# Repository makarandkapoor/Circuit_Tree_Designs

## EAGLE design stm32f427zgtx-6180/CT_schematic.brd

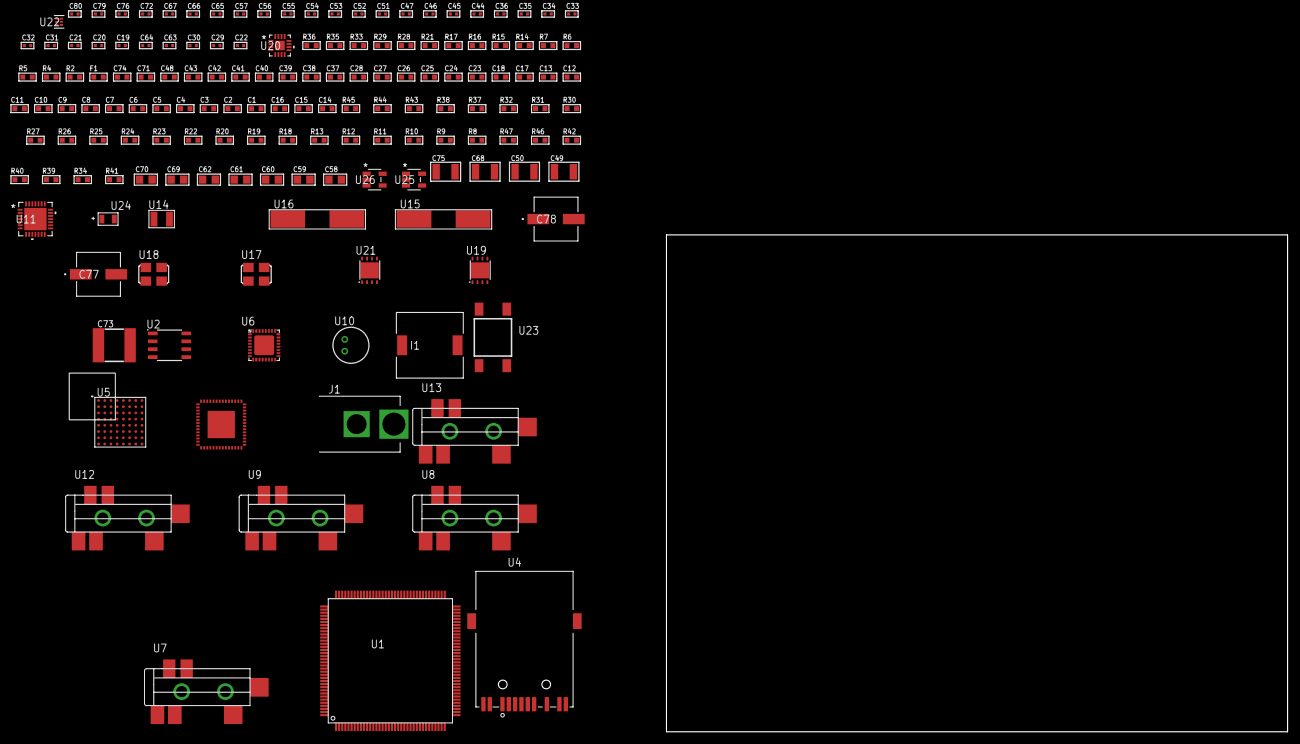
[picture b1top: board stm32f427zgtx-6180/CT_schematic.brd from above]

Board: 2 copper layers, 100.0 x 80.0 mm, 154 parts (0 on the bottom side), 149 nets, no tracks yet.

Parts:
C1, C18, C37, C38, C39, C40, C41, C42, C43, C48, C71: 1e-06; C0603
C2, C3, C4, C5, C6, C7, C8, C9, C10, C11, C12, C13, C23, C24, C25, C26, C27, C28: 1e-07; C0603
C14: 4.7e-06; C0603
C15, C16: 2.2e-06; C0603
C17: 1e-08; C0603
C19, C20: 1e-11; C0402
C21, C32, C34, C36, C65, C66, C67, C79, C80: 1e-08; C0402
C22: 2.2e-08; C0402
C29, C30, C63, C64: 2.2e-11; C0402
C31, C33, C35, C44, C45, C46, C47, C53, C54, C55, C56, C57, C72, C76: 1e-07; C0402
C49, C50: 2.2e-05; C1210
C51, C52: 1e-09; C0402
C58, C59, C60, C61, C62, C69, C70: 1e-05; C0805
C68, C75: 1e-05; C1210
C73: 6.8e-05; 2220
C74: 8e-07; R0603
C77, C78: 0.0001; EXV-9H
F1: 240.0; L0603
I1: 5.2e-06; DR1040
J1: PJ-037B; PJ-037B_PACKAGE
R2, R36: 1000.0; R0603
R4, R5: 4700.0; R0603
R6, R7: 2200.0; R0603
R8, R9, R10, R11, R12, R13, R18, R19, R20, R22, R23, R24, R25, R26, R27, R43, R44: 10000.0; R0603
R14, R15: 0.1; R0603
R16, R17, R35: 200.0; R0603
R21: 2000.0; R0603
R28, R29: 1270.0; R0603
R30, R31, R32: 47000.0; R0603
R33: 680.0; R0603
R34, R40, R42: 100000.0; R0603
R37: 20000.0; R0603
R38: 62000.0; R0603
R39: 300000.0; R0603
R41: 153694.38; R0603
R45: 18000.0; R0603
R46: 470000.0; R0603
R47: 120000.0; R0603
U1: STM32F427ZGT6; LQFP144
U2: AT25512N-SH-T; SOIC-8
U3: 88E3015A2NNP1C000
U4: 7498011122R
U5: PC28F512P33BFD
U6: SGTL5000XNAA3; QFN-32
U7, U8, U9, U12, U13: SJ-43515TS-SMT-TR
U10: WM-64PCT; WM-64PC
U11: WM8731CLSEFL; QFN-28
U14: ABS07-32.768KHZ-7-T
U15: ABLS-25.000MHZ-B2F-T
U16: ABLS-12.288MHZ-B4-T
U17: ASFL-24.57MHZ-NCS; ASFL1
U18: ASFL1-25MHZ-NCS; ASFL1
U19: LP3878SDX-ADJ/NOPB; WSON-8
U20: LTC3601EUD#PBF; QFN-16_EP
U21: LP2951ACSDX/NOPB; WSON-8
U22: TPS3895ADRYR; SON-6
U23: 4-1437565-2; SW_4-1437565-2
U24: Q65110A2395; LGM67K-G1J2-24-Z
U25, U26: nc7sz125m5x; NC7SZ125M5X

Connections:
CLK_CRYSTAL_U1_8: C19.1, U1.8, U14.1
CLK_CRYSTAL_U1_9: C20.1, U1.9, U14.2
CLK_CRYSTAL_U3_32: C29.1, U3.32, U15.1
CLK_CRYSTAL_U3_33: C30.1, U3.33, U15.2
CLK_CRYSTAL_U11_1: C63.1, U11.1, U16.1
CLK_CRYSTAL_U11_2: C64.1, U11.2, U16.2
CLK_U1_23: U1.23, U18.3
CLK_U6_21: U6.21, U17.3
GND: C1.2, C2.2, C3.2, C4.2, C5.2, C6.2, C7.2, C8.2, C9.2, C10.2, C11.2, C12.2, C13.2, C14.2, C15.2, C16.2, C17.2, C18.2, C19.2, C20.2, C21.2, C22.2, C23.2, C24.2, C25.2, C26.2, C27.2, C28.2, C29.2, C30.2, C31.2, C32.2, C33.2, C34.2, C35.2, C36.2, C44.2, C45.2, C46.2, C47.2, C48.2, C52.2, C53.2, C54.2, C55.2, C56.2, C57.2, C58.2, C59.2, C60.2, C61.2, C62.2, C63.2, C64.2, C65.2, C66.2, C67.2, C68.2, C69.2, C70.2, C71.2, C73.1, C73.2, C74.2, C75.2, C76.2, C77.2, C78.2, C79.2, C80.2, J1.2, R2.2, R14.2, R15.2, R21.2, R29.2, R30.2, R31.2, R32.2, R36.2, R37.2, R39.2, R42.2, R45.2, R47.2, U1.16, U1.31, U1.38, U1.51, U1.61, U1.83, U1.94, U1.107, U1.120, U1.130, U2.4, U3.1, U3.2, U3.57, U4.10, U4.12, U5.B2, U5.H2, U5.H4, U5.H6, U6.1, U6.3, U6.7, U6.EXP, U8.1, U9.1, U10.2, U11.4, U11.15, U11.19, U11.25, U11.26, U11.29, U12.1, U13.1, U17.2, U18.2, U19.3, U19.PAD, U20.1, U20.9, U20.17, U21.3, U21.4, U21.PAD, U22.2, U24.C, U25.1, U25.3, U26.1, U26.3
NET_U1_25: R5.1, U1.25, U26.4
NET_U1_27: R6.1, U1.27, U3.38
NET_U1_33: C17.1, C18.1, F1.1, U1.32, U1.33
NET_U1_36: R7.1, U1.36, U3.35
NET_U1_48: R10.1, U1.48
NET_U1_71: C15.1, U1.71
NET_U1_106: C16.1, U1.106
NET_U1_138: R9.1, U1.138
NET_U1_142: U23.3, U23.4
NET_U1_143: R8.1, U1.143
NET_U2_3: R11.1, U2.3
NET_U2_7: R13.1, U2.7
NET_U3_9: R19.1, U3.9
NET_U3_10: R22.1, U3.10
NET_U3_16: R18.1, U3.16
NET_U3_28: R21.1, U3.28
NET_U3_39: R20.1, U3.39
NET_U3_44: U3.44, U3.48, U3.49, U3.56
NET_U4_1: U3.26, U4.1
NET_U4_3: U3.25, U4.3
NET_U4_4: U3.23, U4.4
NET_U4_5: C22.1, U4.2, U4.5
NET_U4_6: U3.22, U4.6
NET_U4_8: R15.1, R17.2, U4.8
NET_U4_9: R16.1, U4.9
NET_U4_11: R17.1, U4.11
NET_U4_13: R14.1, U4.13, U4.14
NET_U5_A4: C35.1, C36.1, U5.A4
NET_U5_C6: R26.1, U5.C6
NET_U5_D4: R4.1, U5.D4, U25.4
NET_U6_10: C47.1, U6.10
NET_U6_29: R28.1, U6.29
NET_U6_31: R29.1, U6.31
NET_U7_1: U6.4, U7.1
NET_U7_2: U6.2, U7.2
NET_U7_5: U6.6, U7.5
NET_U8_2: C38.1, U8.2
NET_U8_5: C37.1, U8.5
NET_U9_2: C40.1, C41.1, U9.2
NET_U9_5: C39.1, U9.5
NET_U9_13: C40.2, C41.2
NET_U10_1: C42.1, C43.1, C48.1, U6.16, U10.1
NET_U10_15: C42.2, C43.2
NET_U11_20: C57.1, C62.1, U11.20
NET_U12_2: C50.1, R31.1, U12.2
NET_U12_5: C49.1, R30.1, U12.5
NET_U13_5: C51.1, C52.1, R32.1, R33.1, U13.5
NET_U19_1: C67.1, U19.1
NET_U19_6: R35.2, R36.1, U19.6
NET_U19_8: R34.1, U19.8
NET_U20_3: C72.2, I1.1, U20.3, U20.4
NET_U20_6: C72.1, U20.6
NET_U20_7: C71.1, U20.7, U20.12
NET_U20_10: R39.1, U20.10
NET_U20_11: R37.1, R38.1, U20.11
NET_U20_ATNET_3: I1.2, R38.2
NET_U21_5: R40.1, U21.5
NET_U21_7: R41.2, R42.1, U21.7
NET_U22_1: R44.1, R45.1, U22.1
NET_U22_3: R46.2, R47.1, U22.3
NET_U22_4: R43.1, U22.4, U25.2, U26.2
NET_U23_1: R2.1, U23.1, U23.2
PROC_ETH_COL: U1.37, U3.3, U3.19
PROC_ETH_CRS: U1.34, U3.18
PROC_ETH_RXD0: U1.44, U3.42
PROC_ETH_RXD1: U1.45, U3.43
PROC_ETH_RXD2: U1.46, U3.46
PROC_ETH_RXD3: U1.47, U3.47
PROC_ETH_RX_CLK: U1.35, U3.45
PROC_ETH_RX_DV: U1.43, U3.41
PROC_ETH_RX_ER: U1.69, U3.17
PROC_ETH_TXD0: U1.73, U3.50
PROC_ETH_TXD1: U1.129, U3.51
PROC_ETH_TXD2: U1.28, U3.53
PROC_ETH_TXD3: U1.139, U3.54
PROC_ETH_TX_CLK: U1.29, U3.52
PROC_ETH_TX_EN: U1.70, U3.55
PROC_FMC_A0: U1.10, U5.A1
PROC_FMC_A1: U1.11, U5.B1
PROC_FMC_A2: U1.12, U5.C1
PROC_FMC_A3: U1.13, U5.D1
PROC_FMC_A4: U1.14, U5.D2
PROC_FMC_A5: U1.15, U5.A2
PROC_FMC_A6: U1.50, U5.C2
PROC_FMC_A7: U1.53, U5.A3
PROC_FMC_A8: U1.54, U5.B3
PROC_FMC_A9: U1.55, U5.C3
PROC_FMC_A10: U1.56, U5.D3
PROC_FMC_A11: U1.57, U5.C4
PROC_FMC_A12: U1.87, U5.A5
PROC_FMC_A13: U1.88, U5.B5
PROC_FMC_A14: U1.89, U5.C5
PROC_FMC_A15: U1.90, U5.D7
PROC_FMC_A16: U1.80, U5.D8
PROC_FMC_A17: U1.81, U5.A7
PROC_FMC_A18: U1.82, U5.B7
PROC_FMC_A19: U1.2, U5.C7
PROC_FMC_A20: U1.3, U5.C8
PROC_FMC_A21: U1.4, U5.A8
PROC_FMC_A22: U1.5, U5.G1
PROC_FMC_A23: U1.1, U5.H8
PROC_FMC_A24: U1.128, U5.B6
PROC_FMC_CLK: U1.117, U5.E6
PROC_FMC_D0: U1.85, U5.F2
PROC_FMC_D1: U1.86, U5.E2
PROC_FMC_D2: U1.114, U5.G3
PROC_FMC_D3: U1.115, U5.E4
PROC_FMC_D4: U1.58, U5.E5
PROC_FMC_D5: U1.59, U5.G5
PROC_FMC_D6: U1.60, U5.G6
PROC_FMC_D7: U1.63, U5.H7
PROC_FMC_D8: U1.64, U5.E1
PROC_FMC_D9: U1.65, U5.E3
PROC_FMC_D10: U1.66, U5.F3
PROC_FMC_D11: U1.67, U5.F4
PROC_FMC_D12: U1.68, U5.F5
PROC_FMC_D13: U1.77, U5.H5
PROC_FMC_D14: U1.78, U5.G7
PROC_FMC_D15: U1.79, U5.E7
PROC_FMC_NE2: R24.1, U1.124, U5.B4
PROC_FMC_NL: R23.1, U1.137, U5.F6
PROC_FMC_NOE: R25.1, U1.118, U5.F8
PROC_FMC_NWAIT: U1.122, U5.F7
PROC_FMC_NWE: R27.1, U1.119, U5.G8
PROC_I2S2_CK: U1.74, U11.7
PROC_I2S2_EXT_SD: U1.75, U11.10
PROC_I2S2_SD: U1.76, U11.8
PROC_I2S2_WS: U1.140, U11.9, U11.11
PROC_I2S3_CK: U1.111, U6.24
PROC_I2S3_EXT_SD: U1.112, U6.25
PROC_I2S3_SD: U1.113, U6.26
PROC_I2S3_WS: U1.110, U6.23
PROC_SPI1_MISO: U1.42, U2.2
PROC_SPI1_MOSI: U1.135, U2.5
PROC_SPI1_NSS: R12.1, U1.40, U2.1
PROC_SPI1_SCK: U1.41, U2.6
VCC_S1_12V9: C68.1, C70.1, C74.1, C77.1, C78.1, J1.1, R34.2, U19.4, U20.15, U20.16, U21.8
VCC_TIER1_1V2: C23.1, C24.1, C44.1, C69.1, R35.1, U3.4, U3.11, U3.34, U6.30, U19.5
VCC_TIER1_2V5: C1.1, C2.1, C3.1, C4.1, C5.1, C6.1, C7.1, C8.1, C9.1, C10.1, C11.1, C12.1, C13.1, C14.1, C21.1, C25.1, C26.1, C27.1, C28.1, C31.1, C32.1, C33.1, C34.1, C45.1, C46.1, C53.1, C54.1, C55.1, C56.1, C58.1, C59.1, C60.1, C61.1, C73.2, C76.1, C79.1, C80.1, F1.2, I1.2, R4.2, R5.2, R6.2, R7.2, R8.2, R9.2, R10.2, R11.2, R12.2, R13.2, R18.2, R19.2, R20.2, R22.2, R23.2, R24.2, R25.2, R26.2, R27.2, R28.2, R38.2, R43.2, R44.2, R46.1, U1.6, U1.17, U1.30, U1.39, U1.52, U1.62, U1.72, U1.84, U1.95, U1.108, U1.121, U1.131, U1.144, U2.8, U3.6, U3.12, U3.13, U3.20, U3.24, U3.29, U3.36, U4.2, U5.A6, U5.D5, U5.D6, U5.G4, U5.H3, U6.5, U6.20, U11.3, U11.5, U11.12, U11.18, U20.8, U22.6, U25.5, U26.5
VCC_TIER1_3V3: C65.1, C66.1, C75.1, R40.2, R41.1, U17.4, U18.4, U21.1

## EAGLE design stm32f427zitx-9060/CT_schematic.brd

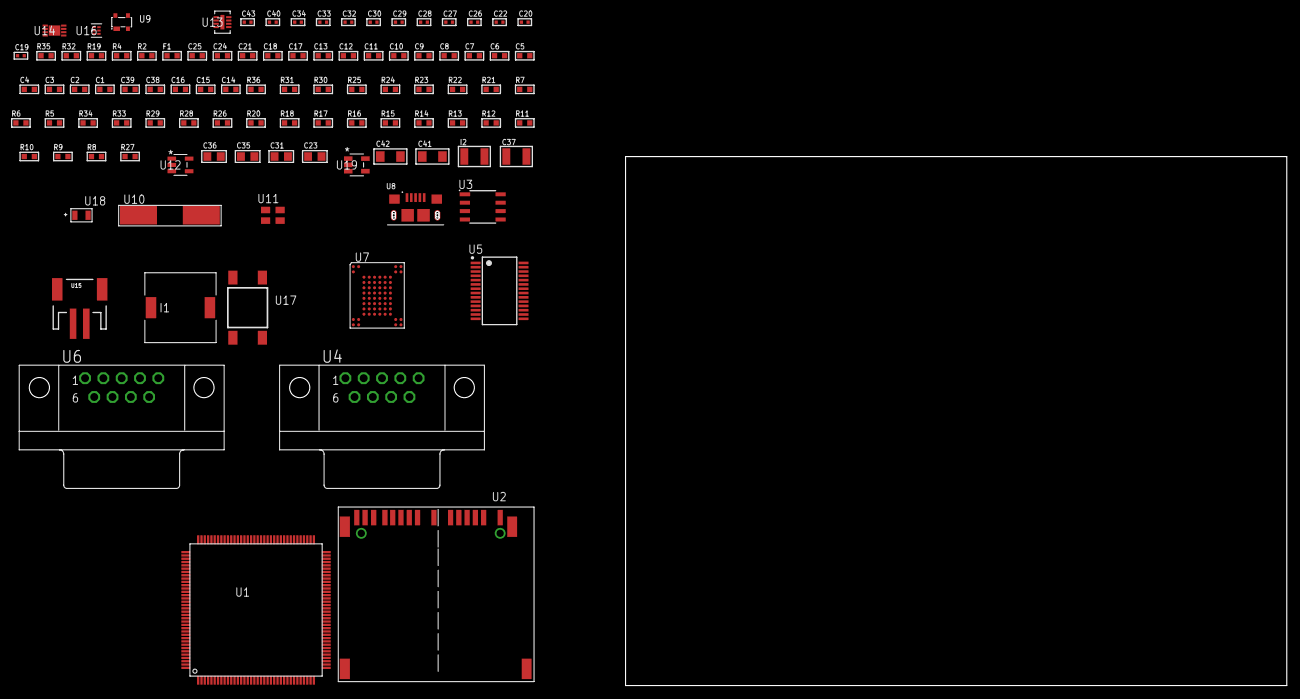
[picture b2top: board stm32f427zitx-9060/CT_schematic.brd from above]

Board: 2 copper layers, 99 parts (0 on the bottom side), 76 nets, no tracks yet.

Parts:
C1, C18, C21, C24, C25: 1e-06; C0603
C2, C3, C4, C5, C6, C7, C8, C9, C10, C11, C12, C13: 1e-07; C0603
C14: 4.7e-06; C0603
C15, C16, C38: 2.2e-06; C0603
C17: 1e-08; C0603
C19, C20: 1e-11; C0402
C22, C26, C27, C28, C29, C30, C32, C33, C40: 1e-07; C0402
C23, C31, C35, C36: 1e-05; C0805
C34, C43: 1e-08; C0402
C37: 1e-05; C1210
C39: 2.2e-07; C0603
C41, C42: 1e-05; C1206
F1: 240.0; L0603
I1: 2.5e-06; DR1040
I2: 1e-05; L1210
R2: 1000.0; R0603
R4: 4700.0; R0603
R5, R6, R7, R21, R22, R23, R24, R25, R30, R31, R36: 10000.0; R0603
R8, R9, R10, R11, R12, R13, R14, R15, R16, R17, R18, R20, R28: 100000.0; R0603
R19: 120.0; R0603
R26: 220000.0; R0603
R27: 1000000.0; R0603
R29: 560000.0; R0603
R32: 9100.0; R0603
R33: 680000.0; R0603
R34: 120000.0; R0603
R35: 2000.0; R0603
U1: STM32F427ZIT7; LQFP144
U2: 10100565
U3: MCP2562-E/SN; SOIC-8
U4, U6: 182-009-113R531; 182-009-MALE
U5: ST3241EBPR; SSOP-28
U7: TH58NVG3S0HBAI4
U8: 10118193-0001LF; FCI_10118193-0001LF
U9: prtr5v0u2ax; SOT143B
U10: ABLS-25.000MHZ-B2F-T
U11: ASEK-32.768KHz-ECST; ASEK
U12: ltc3406es5; TSOT-23-5
U13: LT3494AEDDB#TRMPBF; DFN-8_DDB
U14: MCP73831T-2ACI/MC; DFN8_2X3MC
U15: S2B-PH-SM4-TB(LF)(SN); JST-2-SMD
U16: TPS3895ADRYR; SON-6
U17: 4-1437565-2; SW_4-1437565-2
U18: Q65110A2395; LGM67K-G1J2-24-Z
U19: nc7sz125m5x; NC7SZ125M5X

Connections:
CLK_CRYSTAL_U1_23: C19.1, U1.23, U10.1
CLK_CRYSTAL_U1_24: C20.1, U1.24, U10.2
CLK_U1_8: U1.8, U11.3
GND: C1.2, C2.2, C3.2, C4.2, C5.2, C6.2, C7.2, C8.2, C9.2, C10.2, C11.2, C12.2, C13.2, C14.2, C15.2, C16.2, C17.2, C18.2, C19.2, C20.2, C21.2, C22.2, C23.2, C24.2, C25.2, C26.2, C29.2, C30.2, C31.2, C32.2, C33.2, C34.2, C35.2, C36.1, C36.2, C37.2, C38.2, C39.2, C40.2, C41.2, C42.2, C43.2, R2.2, R7.2, R26.2, R32.2, R34.2, R35.2, U1.16, U1.31, U1.38, U1.51, U1.61, U1.83, U1.94, U1.103, U1.107, U1.120, U1.130, U2.6, U2.10, U2.12, U2.16, U2.17, U2.20, U2.21, U3.2, U3.8, U4.5, U5.23, U5.25, U6.5, U7.C5, U7.K3, U7.K8, U8.5, U8.6, U8.7, U8.8, U8.9, U9.1, U11.2, U12.2, U13.2, U13.9, U14.6, U14.9, U15.2, U16.2, U18.C, U19.1, U19.3
INPUT_USBPOWER_5V: C21.1, C41.1, R36.2, U1.101, U8.1, U9.4, U14.1, U14.2
NET_U1_25: R4.1, U1.25, U19.4
NET_U1_33: C17.1, C18.1, F1.1, U1.32, U1.33
NET_U1_48: R7.1, U1.48
NET_U1_71: C15.1, U1.71
NET_U1_106: C16.1, U1.106
NET_U1_138: R6.1, U1.138
NET_U1_142: U17.3, U17.4
NET_U1_143: R5.1, U1.143
NET_U2_1: R10.1, U2.1
NET_U2_2: R9.1, U2.2
NET_U2_18: U2.18, U2.19
NET_U3_6: R19.2, U3.6
NET_U4_2: R19.2, U3.6, U4.2
NET_U4_3: R19.1, U3.7, U4.3
NET_U5_1: C28.1, U5.1
NET_U5_2: C28.2, U5.2
NET_U5_3: C30.1, U5.3
NET_U5_22: R20.1, U5.22
NET_U5_24: C27.2, U5.24
NET_U5_27: C29.1, U5.27
NET_U5_28: C27.1, U5.28
NET_U6_2: U5.4, U6.2
NET_U6_3: U5.9, U6.3
NET_U6_7: U5.5, U6.7
NET_U6_8: U5.10, U6.8
NET_U7_C3: R24.1, U7.C3
NET_U12_3: I1.1, U12.3
NET_U12_5: R26.1, R27.1, U12.5
NET_U12_ATNET_3: I1.2, R27.2
NET_U13_1: I2.1, U13.1
NET_U13_5: R28.1, U13.5
NET_U13_6: R29.1, U13.6
NET_U13_8: C39.1, U13.8
NET_U14_5: R36.1, U14.5
NET_U14_8: R35.1, U14.8
NET_U16_1: R31.1, R32.1, U16.1
NET_U16_3: R33.2, R34.1, U16.3
NET_U16_4: R30.1, U16.4, U19.2
NET_U17_1: R2.1, U17.1, U17.2
PROC_CAN2_RX: U1.73, U3.4
PROC_CAN2_TX: U1.74, U3.1
PROC_FMC_A16: U1.80, U7.D5
PROC_FMC_A17: U1.81, U7.C4
PROC_FMC_D0: U1.85, U7.H4
PROC_FMC_D1: U1.86, U7.J4
PROC_FMC_D2: U1.114, U7.K4
PROC_FMC_D3: U1.115, U7.K5
PROC_FMC_D4: U1.58, U7.K6
PROC_FMC_D5: U1.59, U7.J7
PROC_FMC_D6: U1.60, U7.K7
PROC_FMC_D7: U1.63, U7.J8
PROC_FMC_INT2: R25.1, U1.91, U7.C8
PROC_FMC_NCE2: R21.1, U1.123, U7.C6
PROC_FMC_NOE: R22.1, U1.118, U7.D4
PROC_FMC_NWE: R23.1, U1.119, U7.C7
PROC_SDIO_CK: R8.1, U1.113, U2.8
PROC_SDIO_D0: R11.1, U1.98, U2.4
PROC_SDIO_D1: R12.1, U1.99, U2.3
PROC_SDIO_D2: R13.1, U1.111, U2.15
PROC_SDIO_D3: R14.1, U1.112, U2.14
PROC_SDIO_D4: R15.1, U1.139, U2.13
PROC_SDIO_D5: R16.1, U1.140, U2.11
PROC_SDIO_D6: R17.1, U1.96, U2.7
PROC_SDIO_D7: R18.1, U1.97, U2.5
PROC_UART4_RX: U1.35, U5.19
PROC_UART4_TX: U1.34, U5.14
PROC_USB_OTG_FS_DM: U1.103, U8.2, U9.3
PROC_USB_OTG_FS_DP: U1.104, U8.3, U9.2
VCC_S1_3V7: C35.1, C37.1, C42.1, I2.2, R28.2, U12.4, U13.3, U13.4, U14.3, U14.4, U15.1
VCC_TIER1_3V3: C1.1, C2.1, C3.1, C4.1, C5.1, C6.1, C7.1, C8.1, C9.1, C10.1, C11.1, C12.1, C13.1, C14.1, C22.1, C23.1, C25.1, C26.1, C31.1, C32.1, C33.1, C34.1, C36.2, C40.1, C43.1, F1.2, I1.2, R4.2, R5.2, R6.2, R8.2, R9.2, R10.2, R11.2, R12.2, R13.2, R14.2, R15.2, R16.2, R17.2, R18.2, R20.2, R21.2, R22.2, R23.2, R24.2, R25.2, R27.2, R30.2, R31.2, R33.1, U1.6, U1.17, U1.30, U1.39, U1.52, U1.62, U1.72, U1.84, U1.95, U1.108, U1.121, U1.131, U1.144, U2.9, U3.5, U5.26, U7.H8, U7.J6, U11.4, U16.6, U19.5
VCC_TIER1_5V0: C24.1, C38.1, R29.2, U3.3, U13.7

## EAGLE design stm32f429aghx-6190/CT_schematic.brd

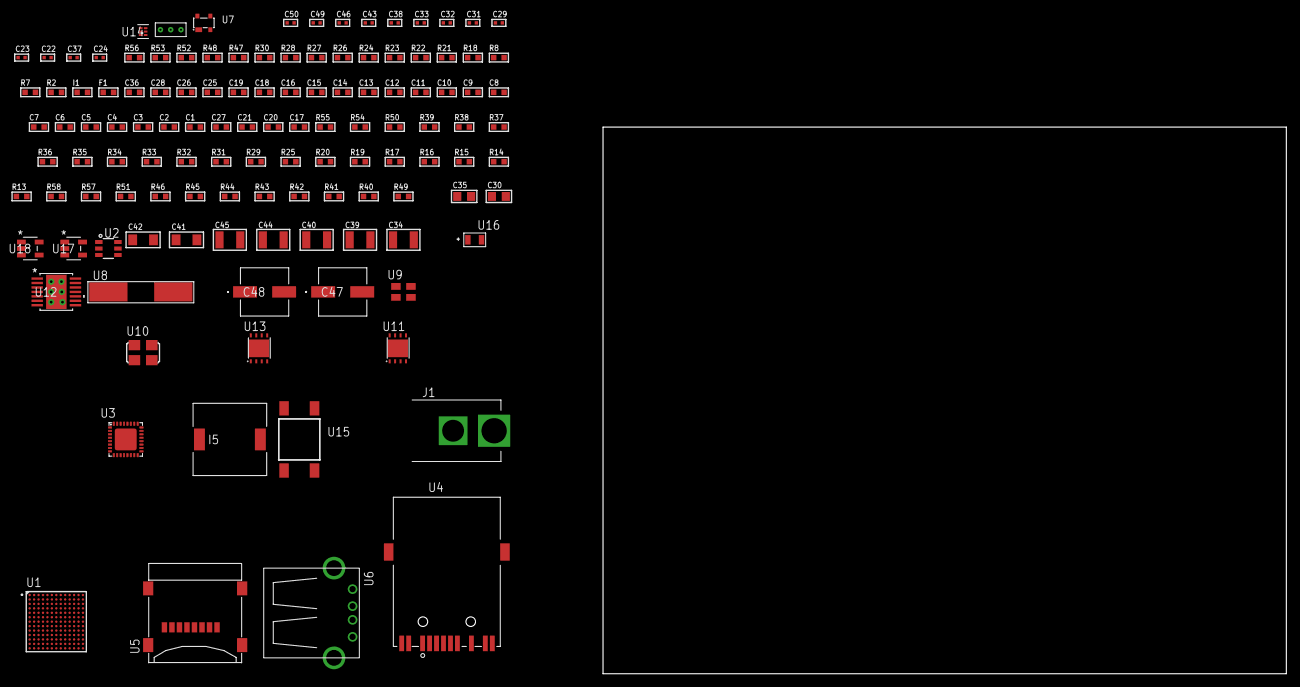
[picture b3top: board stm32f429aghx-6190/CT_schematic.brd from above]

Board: 2 copper layers, 100.0 x 80.0 mm, 122 parts (0 on the bottom side), 70 nets, no tracks yet.

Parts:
C1, C19, C25, C26, C28, C36: 1e-06; C0603
C2, C3, C4, C5, C6, C7, C8, C9, C10, C11, C12, C13, C14, C15, C16: 1e-07; C0603
C17: 4.7e-06; C0603
C18: 1e-08; C0603
C20, C21: 2.2e-06; C0603
C22, C23: 1e-11; C0402
C24: 2.2e-08; C0402
C27: 4.7e-10; C0603
C29, C38, C46: 1e-07; C0402
C30, C35: 1e-05; C0805
C31, C32, C33, C43, C49, C50: 1e-08; C0402
C34, C44, C45: 1e-05; C1210
C37: 3.3e-09; C0402
C39, C40: 2.2e-05; C1210
C41, C42: 1e-05; C1206
C47, C48: 0.0001; EXV-9H
F1: 240.0; L0603
I1: 97.0; R0603
I5: 3.8e-06; DR1040
J1: PJ-037B; PJ-037B_PACKAGE
R2, R48, R53: 1000.0; R0603
R7, R8: 4700.0; R0603
R13: 47000.0; R0603
R14, R15, R16, R17, R19, R20, R29, R31, R32, R33, R34, R35, R36, R37, R38, R39, R54, R55: 10000.0; R0603
R18: 1270.0; R0603
R21, R22: 0.1; R0603
R23, R24, R47: 200.0; R0603
R25: 12100.0; R0603
R26, R27, R28, R30: 49.9; R0603
R40, R41, R42, R43, R44, R45, R46, R51: 100000.0; R0603
R49: 71007.101651032; R0603
R50: 22000.0; R0603
R52: 3900.0; R0603
R56: 9100.0; R0603
R57: 680000.0; R0603
R58: 120000.0; R0603
U1: STM32F429AGH6; UFBGA169
U2: MAX4995AAUT+T; SOT-23-6
U3: LAN8710AI-EZK; QFN-32
U4: 7498011122R
U5: 0472192001; MOLEX_47219-2001
U6: 61400416021; USB-A-H
U7: prtr5v0u2ax; SOT143B
U8: ABLS-25.000MHZ-B2F-T
U9: ASEK-32.768KHz-ECST; ASEK
U10: ASFL1-50MHZ-NCS; ASFL1
U11, U13: LP3878SDX-ADJ/NOPB; WSON-8
U12: TPS54425PWP; HTSSOP14
U14: TPS3895ADRYR; SON-6
U15: 4-1437565-2; SW_4-1437565-2
U16: Q65110A2395; LGM67K-G1J2-24-Z
U17, U18: nc7sz125m5x; NC7SZ125M5X
U19: Dummy; DUMMY_PACKAGE_243

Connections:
CLK_CRYSTAL_U1_G1: C22.1, U1.G1, U8.1
CLK_CRYSTAL_U1_G2: C23.1, U1.G2, U8.2
CLK_U1_E1: U1.E1, U9.3
CLK_U1_K1: U1.K1, U10.3
GND: C1.2, C2.2, C3.2, C4.2, C5.2, C6.2, C7.2, C8.2, C9.2, C10.2, C11.2, C12.2, C13.2, C14.2, C15.2, C16.2, C17.2, C18.2, C19.2, C20.2, C21.2, C22.2, C23.2, C24.2, C25.2, C26.2, C27.2, C28.2, C29.2, C30.2, C31.2, C32.2, C33.2, C34.2, C35.2, C36.2, C37.2, C39.2, C40.2, C41.2, C42.2, C43.2, C44.2, C45.2, C46.2, C47.2, C48.2, C49.2, C50.2, J1.2, R2.2, R13.2, R17.2, R18.2, R20.2, R21.2, R22.2, R23.2, R25.2, R31.2, R38.2, R39.2, R48.2, R50.2, R53.2, R56.2, R58.2, U1.D7, U1.D11, U1.E7, U1.F5, U1.F6, U1.G7, U1.G9, U1.J1, U1.J2, U1.J6, U1.J7, U1.J10, U2.2, U3.24, U3.25, U3.EXP, U5.6, U5.G1, U5.G2, U5.G3, U5.G4, U6.4, U6.5, U6.6, U7.1, U9.2, U10.2, U11.3, U11.PAD, U12.5, U12.8, U12.9, U12.15, U13.3, U13.PAD, U14.2, U16.C, U17.1, U17.3, U18.1, U18.3, U19.1
NET_U1_A5: R15.1, U1.A5
NET_U1_C3: R14.1, U1.C3
NET_U1_D12: C21.1, U1.D12
NET_U1_E9: R18.1, U1.E9
NET_U1_H2: R8.1, U1.H2, U18.4
NET_U1_J4: C18.1, C19.1, F1.1, U1.J3, U1.J4
NET_U1_L5: R16.1, U1.L5
NET_U1_M1: R17.1, U1.M1
NET_U1_N9: C20.1, U1.N9
NET_U1_N11: U15.3, U15.4
NET_U2_3: R13.1, U2.3
NET_U3_1: C25.1, I1.1, R26.2, R27.2, R28.2, R30.2, R33.2, U3.1, U3.27, U4.2, U4.9
NET_U3_3: R33.1, U3.3
NET_U3_7: R38.1, U3.7
NET_U3_8: R39.1, U3.8
NET_U3_9: R31.1, R32.1, U3.9
NET_U3_13: R37.1, U3.13
NET_U3_18: R29.1, U3.18
NET_U3_19: R7.1, U3.19, U17.4
NET_U3_32: R25.1, U3.32
NET_U4_1: R26.1, U3.29, U4.1
NET_U4_3: R24.2, R27.1, U3.28, U4.3
NET_U4_4: R28.1, U3.31, U4.4
NET_U4_5: C24.1, U4.2, U4.5
NET_U4_6: R30.1, U3.30, U4.6
NET_U4_8: R22.1, U4.8
NET_U4_10: R24.1, U4.10
NET_U4_11: U3.2, U4.11
NET_U4_12: R23.1, U4.12
NET_U4_13: R21.1, U4.13, U4.14
NET_U11_1: C33.1, U11.1
NET_U11_6: R47.2, R48.1, U11.6
NET_U11_8: R46.1, U11.8
NET_U12_2: R49.2, R50.1, U12.2
NET_U12_3: C36.1, U12.3
NET_U12_4: C37.1, U12.4
NET_U12_10: C38.1, I5.1, U12.10, U12.11
NET_U12_12: C38.2, U12.12
NET_U13_1: C43.1, U13.1
NET_U13_6: R52.2, R53.1, U13.6
NET_U13_8: R51.1, U13.8
NET_U14_1: R55.1, R56.1, U14.1
NET_U14_3: R57.2, R58.1, U14.3
NET_U14_4: R54.1, U14.4, U17.2, U18.2
NET_U15_1: R2.1, U15.1, U15.2
PROC_ETH_CRS_DV: R36.1, U3.15
PROC_ETH_RXD0: R34.1, U3.11
PROC_ETH_RXD1: R35.1, U3.10
PROC_GPIO_TO_U1_USB_FAULT: R19.1, U1.A3, U2.6
PROC_GPIO_TO_U1_VBUS_EN: R20.1, U1.A2, U2.4
PROC_SDIO_CK: R41.1, U1.A10, U5.5
PROC_SDIO_CMD: R40.1, U1.B9, U5.3
PROC_SDIO_D0: R42.1, U1.F11, U5.7
PROC_SDIO_D1: R43.1, U1.F12, U5.8
PROC_SDIO_D2: R44.1, U1.C10, U5.1
PROC_SDIO_D3: R45.1, U1.B10, U5.2
PROC_TIM1_CH1: U1.E13, U19.2
PROC_TIM1_CH2N: U1.L8, U19.3
PROC_USB_OTG_FS_DM: U1.E10, U6.2, U7.3
PROC_USB_OTG_FS_DP: U1.E11, U6.3, U7.2
PROC_USB_OTG_FS_VBUS: U1.E8, U2.1, U6.1, U7.4
VCC_S1_14V5: C34.1, C41.1, C42.1, C44.1, C47.1, C48.1, J1.1, R46.2, R51.2, U11.4, U12.7, U12.13, U12.14, U13.4
VCC_TIER1_1V2: C26.1, C27.1, C35.1, R47.1, U3.6, U11.5
VCC_TIER1_3V3: C1.1, C2.1, C3.1, C4.1, C5.1, C6.1, C7.1, C8.1, C9.1, C10.1, C11.1, C12.1, C13.1, C14.1, C15.1, C16.1, C17.1, C28.1, C29.1, C30.1, C31.1, C32.1, C39.1, C40.1, C46.1, C49.1, C50.1, F1.2, I1.2, I5.2, R7.2, R8.2, R14.2, R15.2, R16.2, R19.2, R29.2, R32.2, R34.2, R35.2, R36.2, R37.2, R40.2, R41.2, R42.2, R43.2, R44.2, R45.2, R49.1, R54.2, R55.2, R57.1, U1.D3, U1.D6, U1.D10, U1.E5, U1.E6, U1.F4, U1.F7, U1.F8, U1.G8, U1.G10, U1.H4, U1.H8, U1.J11, U1.K6, U1.L6, U3.12, U5.4, U9.4, U10.4, U12.1, U14.6, U17.5, U18.5
VCC_TIER1_5V0: C45.1, R52.1, U2.5, U13.5

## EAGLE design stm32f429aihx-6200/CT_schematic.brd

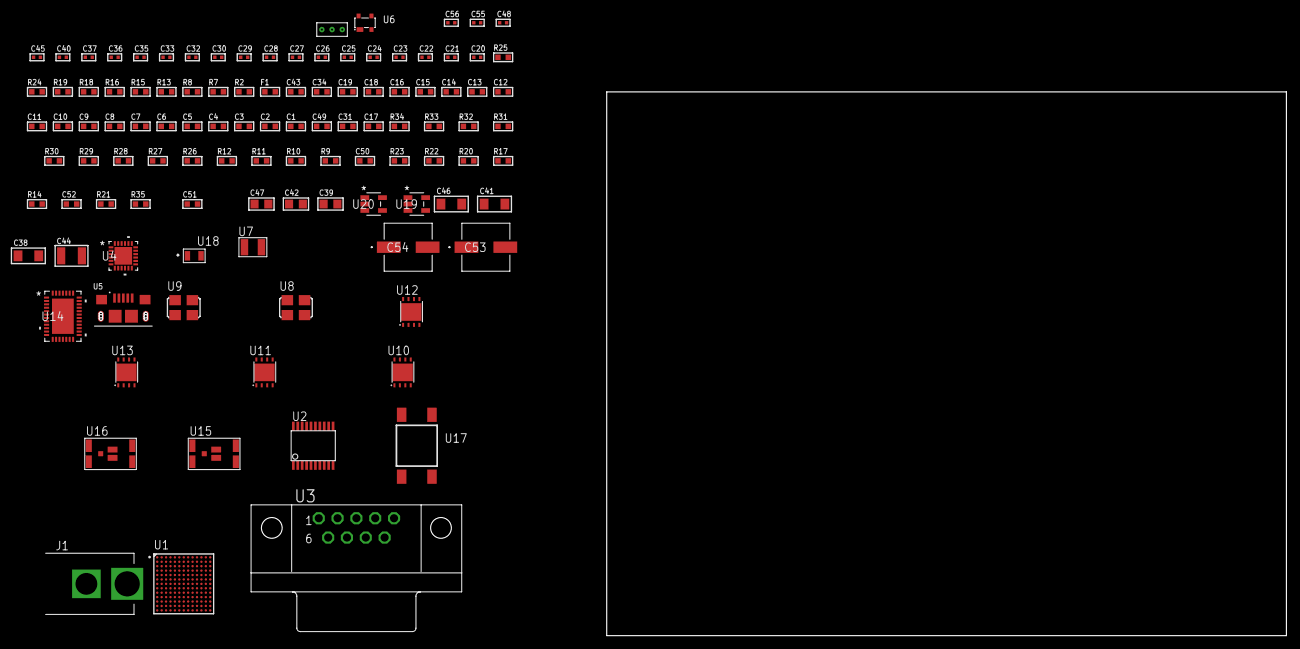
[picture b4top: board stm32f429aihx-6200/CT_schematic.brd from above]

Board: 2 copper layers, 109 parts (0 on the bottom side), 78 nets, no tracks yet.

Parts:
C1, C19, C34, C43: 1e-06; C0603
C2, C3, C4, C5, C6, C7, C8, C9, C10, C11, C12, C13, C14, C15, C16: 1e-07; C0603
C17: 4.7e-06; C0603
C18: 1e-08; C0603
C20, C21, C24, C25, C26, C27, C28, C29, C48: 1e-07; C0402
C22, C23: 1e-11; C0402
C30, C32, C33, C35, C36, C37, C40, C45, C55, C56: 1e-08; C0402
C31, C49: 2.2e-06; C0603
C38, C41, C46: 1e-05; C1206
C39, C42, C47: 1e-05; C0805
C44: 1e-05; C1210
C50: 2.45e-08; R0603
C51: 2.8258362168397e-09; R0603
C52: 7.105e-09; R0603
C53, C54: 0.0001; EXV-9H
F1: 240.0; L0603
J1: PJ-037B; PJ-037B_PACKAGE
R2, R16, R19, R25: 1000.0; R0603
R7, R8: 4700.0; R0603
R9, R10, R11, R12, R26, R28, R29, R32, R33, R34: 10000.0; R0603
R13: 8060.0; R0603
R14, R17, R20, R22, R23: 100000.0; R0603
R15, R24: 200.0; R0603
R18: 806.0; R0603
R21: 153694.38; R0603
R27: 75000.0; R0603
R30, R31: 95300.0; R0603
R35: 70381.818181818; R0603
U1: STM32F429AIH6; UFBGA169
U2: SP3203ECY-L/TR; TSSOP20-I
U3: 182-009-113R531; 182-009-MALE
U4: USB3317C-CP-TR; QFN-24
U5: 10118193-0001LF; FCI_10118193-0001LF
U6: prtr5v0u2ax; SOT143B
U7: ABS07-32.768KHZ-7-T
U8: ASFL1-25MHZ-NCS; ASFL1
U9: ASFL1-26MHZ-NCS; ASFL1
U10, U11, U13: LP3878SDX-ADJ/NOPB; WSON-8
U12: LP2951ACSDX/NOPB; WSON-8
U14: LTC2928CUHF#PBF; QFN-38_UHF
U15, U16: IRF8306MTRPbF; IRF8306MTRPBF
U17: 4-1437565-2; SW_4-1437565-2
U18: Q65110A2395; LGM67K-G1J2-24-Z
U19, U20: nc7sz125m5x; NC7SZ125M5X
U21: Dummy; DUMMY_PACKAGE_236

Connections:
CLK_CRYSTAL_U1_E1: C22.1, U1.E1, U7.1
CLK_CRYSTAL_U1_F1: C23.1, U1.F1, U7.2
CLK_U1_G2: U1.G2, U8.3
CLK_U4_23: U4.23, U9.3
GND: C1.2, C2.2, C3.2, C4.2, C5.2, C6.2, C7.2, C8.2, C9.2, C10.2, C11.2, C12.2, C13.2, C14.2, C15.2, C16.2, C17.2, C18.2, C19.2, C20.2, C21.2, C22.2, C23.2, C24.2, C25.2, C28.2, C29.2, C30.2, C31.2, C32.2, C33.2, C34.2, C35.2, C36.2, C37.2, C38.2, C39.2, C40.2, C41.2, C42.2, C43.2, C44.2, C45.2, C46.2, C47.2, C48.2, C49.2, C50.2, C51.2, C52.2, C53.2, C54.2, C55.2, C56.2, J1.2, R2.2, R11.2, R13.2, R16.2, R19.2, R22.2, R25.2, R27.2, R30.2, R31.2, R32.2, R33.2, R34.2, U1.D7, U1.D11, U1.E7, U1.F5, U1.F6, U1.G7, U1.G9, U1.J1, U1.J2, U1.J6, U1.J7, U1.J10, U2.18, U3.5, U4.25, U5.5, U5.6, U5.7, U5.8, U5.9, U6.1, U8.2, U9.2, U10.3, U10.PAD, U11.3, U11.PAD, U12.3, U12.4, U12.PAD, U13.3, U13.PAD, U14.8, U14.9, U14.10, U14.12, U14.13, U14.24, U14.25, U14.30, U14.32, U14.39, U18.C, U19.1, U19.3, U20.1, U20.3, U21.1
NET_U1_A5: R10.1, U1.A5
NET_U1_C3: R9.1, U1.C3
NET_U1_D12: C21.1, U1.D12
NET_U1_H2: R7.1, U1.H2, U19.4
NET_U1_J4: C18.1, C19.1, F1.1, U1.J3, U1.J4
NET_U1_L5: R11.1, U1.L5
NET_U1_M1: R12.1, U1.M1
NET_U1_N11: U17.3, U17.4
NET_U2_1: C26.1, U2.1
NET_U2_2: C28.1, U2.2
NET_U2_3: C26.2, U2.3
NET_U2_4: C27.1, U2.4
NET_U2_5: C27.2, U2.5
NET_U2_6: C29.1, U2.6
NET_U3_2: U2.14, U3.2
NET_U3_3: U2.17, U3.3
NET_U3_7: U2.13, U3.7
NET_U3_8: U2.16, U3.8
NET_U4_4: C31.1, U4.4
NET_U4_22: R8.1, U4.22, U20.4
NET_U4_24: R13.1, U4.24
NET_U5_1: C34.1, U4.2, U5.1, U6.4
NET_U5_2: U4.5, U5.2, U6.3
NET_U5_3: U4.6, U5.3, U6.2
NET_U10_1: C37.1, U10.1
NET_U10_6: R15.2, R16.1, U10.6
NET_U10_8: R14.1, U10.8
NET_U11_1: C40.1, U11.1
NET_U11_6: R18.2, R19.1, U11.6
NET_U11_8: R17.1, U11.8
NET_U12_5: R20.1, U12.5
NET_U12_7: R21.2, R22.1, U12.7
NET_U13_1: C45.1, U13.1
NET_U13_6: R24.2, R25.1, U13.6
NET_U13_8: R23.1, U13.8
NET_U14_3: R33.1, U14.3
NET_U14_6: R30.1, U14.6
NET_U14_7: R31.1, U14.7
NET_U14_16: R32.1, R35.1, U14.16
NET_U14_18: R29.1, U14.18
NET_U14_19: R28.1, U14.19, U14.20
NET_U14_21: R26.1, R27.1, U14.21, U19.2, U20.2
NET_U14_22: C48.1, R26.2, R28.2, R29.2, U14.11, U14.22
NET_U14_26: C51.1, U14.26
NET_U14_27: C50.1, U14.27
NET_U14_28: C52.1, U14.28
NET_U14_38: R34.1, U14.38
NET_U15_3: U14.2, U15.3
NET_U16_3: U14.37, U16.3
NET_U17_1: R2.1, U17.1, U17.2
PROC_TIM1_CH1: U1.E13, U21.3
PROC_TIM1_CH2: U1.E8, U21.2
PROC_UART4_RX: U1.B10, U2.11
PROC_UART4_TX: U1.C10, U2.7
PROC_USB_OTG_HS_ULPI_CK: U1.M3, U4.12
PROC_USB_OTG_HS_ULPI_D0: U1.K3, U4.16
PROC_USB_OTG_HS_ULPI_D1: U1.N4, U4.15
PROC_USB_OTG_HS_ULPI_D2: U1.K5, U4.14
PROC_USB_OTG_HS_ULPI_D3: U1.L9, U4.13
PROC_USB_OTG_HS_ULPI_D4: U1.M9, U4.11
PROC_USB_OTG_HS_ULPI_D5: U1.N12, U4.10
PROC_USB_OTG_HS_ULPI_D6: U1.M12, U4.9
PROC_USB_OTG_HS_ULPI_D7: U1.D5, U4.8
PROC_USB_OTG_HS_ULPI_DIR: U1.H6, U4.19
PROC_USB_OTG_HS_ULPI_NXT: U1.H7, U4.18
PROC_USB_OTG_HS_ULPI_STP: U1.G6, U4.20
VCC_9V0: C49.1, C53.1, C54.1, J1.1, R35.2, U14.23, U15.1, U15.2, U15.6, U15.7, U16.1, U16.2, U16.6, U16.7
VCC_S1_9V0: C38.1, C41.1, C43.1, R14.2, R17.2, U10.4, U11.4, U12.8, U15.4, U15.5
VCC_S2_9V0: C46.1, R23.2, U13.4, U16.4, U16.5
VCC_TIER1_1V2: C20.1, C39.1, R15.1, U1.N9, U10.5
VCC_TIER1_1V8: C1.1, C2.1, C3.1, C4.1, C5.1, C6.1, C7.1, C8.1, C9.1, C10.1, C11.1, C12.1, C13.1, C14.1, C15.1, C16.1, C17.1, C25.1, C32.1, C33.1, C42.1, C55.1, C56.1, F1.2, R7.2, R8.2, R9.2, R10.2, R12.2, R18.1, U1.D3, U1.D6, U1.D10, U1.E5, U1.E6, U1.F4, U1.F7, U1.F8, U1.G8, U1.G10, U1.H4, U1.H8, U1.J11, U1.K6, U1.L6, U2.12, U4.17, U4.21, U11.5, U19.5, U20.5
VCC_TIER1_3V3: C24.1, C30.1, C35.1, C36.1, C44.1, R20.2, R21.1, U2.19, U4.3, U8.4, U9.4, U12.1
VCC_TIER2_1V2: C47.1, R24.1, U13.5

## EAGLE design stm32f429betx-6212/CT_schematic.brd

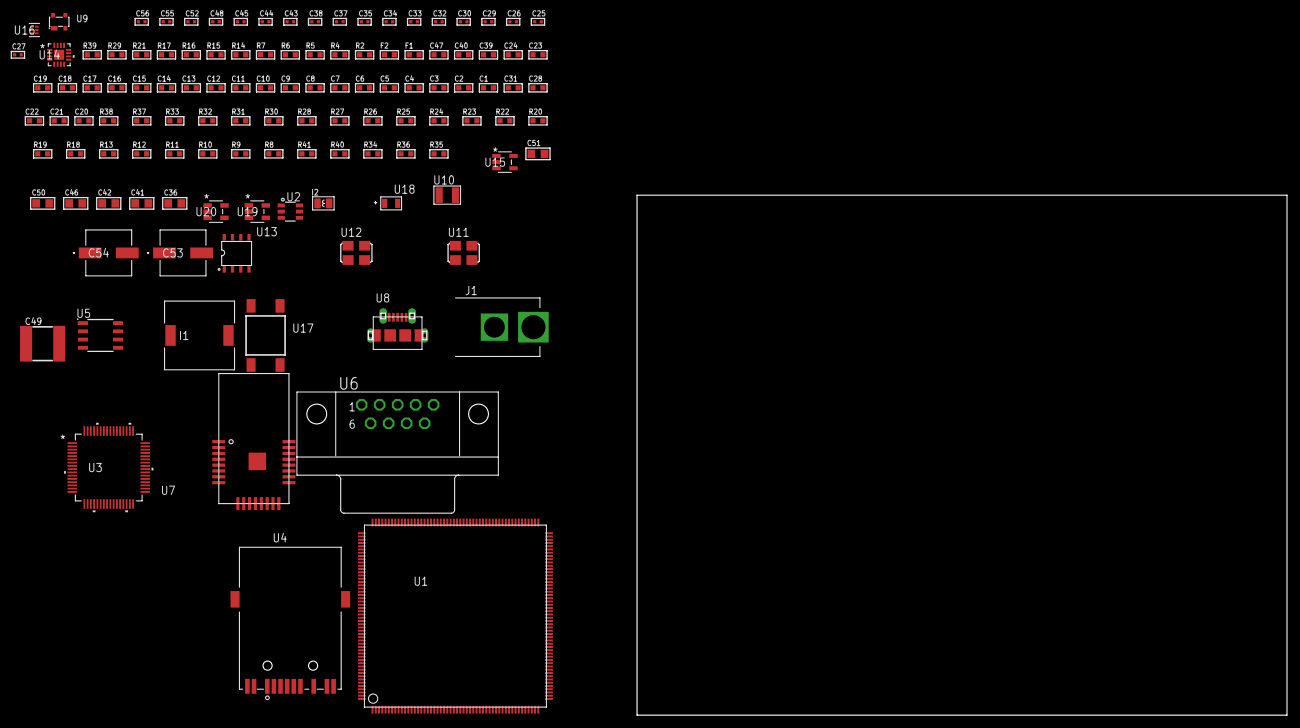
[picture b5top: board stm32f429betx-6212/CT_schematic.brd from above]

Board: 2 copper layers, 120 parts (0 on the bottom side), 82 nets, no tracks yet.

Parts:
C1, C24, C39, C40, C47: 1e-06; C0603
C2, C3, C4, C5, C6, C7, C8, C9, C10, C11, C12, C13, C14, C15, C16, C17, C18, C19: 1e-07; C0603
C20: 4.7e-06; C0603
C21, C22: 2.2e-09; C0603
C23: 1e-08; C0603
C25, C26: 1e-11; C0402
C27: 1.8e-08; C0402
C28, C31: 2.2e-06; C0603
C29, C32, C34, C35, C37, C38, C48, C52: 1e-07; C0402
C30, C33, C43, C44, C45, C55, C56: 1e-08; C0402
C36, C41, C42, C46, C50, C51: 1e-05; C0805
C49: 6.8e-05; 2220
C53, C54: 0.0001; EXV-9H
F1: 240.0; L0603
F2: 510.0; L0603
I1: 3.8e-06; DR1040
I2: 1.5e-06; L0806
J1: PJ-037B; PJ-037B_PACKAGE
R2: 1000.0; R0603
R4, R5: 4700.0; R0603
R6, R7: 2200.0; R0603
R8: 47000.0; R0603
R9, R10, R11, R12, R13, R18, R19, R20, R22, R23, R24, R25, R26, R27, R28, R30, R31, R37, R38: 10000.0; R0603
R14, R15: 0.1; R0603
R16, R17: 200.0; R0603
R21: 1270.0; R0603
R29: 120.0; R0603
R32: 20000.0; R0603
R33: 91000.0; R0603
R34: 300000.0; R0603
R35: 133636.36363636; R0603
R36: 1000000.0; R0603
R39: 9100.0; R0603
R40: 680000.0; R0603
R41: 120000.0; R0603
U1: STM32F429BET6; LQFP208
U2: MAX4995AAUT+T; SOT-23-6
U3: BCM5221KPT; TQFP64_10X10MC
U4: 7498011122R
U5: MCP2562-E/SN; SOIC-8
U6: 182-009-113R531; 182-009-MALE
U7: ATBTLC1000-MR110CA
U8: 47590-0001; MICRO_USB_AB
U9: prtr5v0u2ax; SOT143B
U10: ABS07-32.768KHZ-7-T
U11: ASFL1-25MHZ-NCS; ASFL1
U12: ASFL1-50MHZ-NCS; ASFL1
U13: idt74fct38072; IDT74FCT38072
U14: LTC3601EUD#PBF; QFN-16_EP
U15: ltc3406es5; TSOT-23-5
U16: TPS3895ADRYR; SON-6
U17: 4-1437565-2; SW_4-1437565-2
U18: Q65110A2395; LGM67K-G1J2-24-Z
U19, U20: nc7sz125m5x; NC7SZ125M5X

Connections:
CLK_CRYSTAL_U1_9: C25.1, U1.9, U10.1
CLK_CRYSTAL_U1_10: C26.1, U1.10, U10.2
CLK_U1_32: U1.32, U11.3
CLK_U1_44: U1.44, U13.7
CLK_U3_4: U3.4, U13.6
CLK_U13_3: U12.3, U13.3
GND: C1.2, C2.2, C3.2, C4.2, C5.2, C6.2, C7.2, C8.2, C9.2, C10.2, C11.2, C12.2, C13.2, C14.2, C15.2, C16.2, C17.2, C18.2, C19.2, C20.2, C21.2, C22.2, C23.2, C24.2, C25.2, C26.2, C27.2, C28.2, C29.2, C30.2, C31.2, C32.2, C33.2, C34.2, C35.2, C36.2, C37.2, C38.2, C39.2, C40.2, C41.2, C42.2, C43.2, C44.2, C45.2, C46.2, C47.2, C49.1, C49.2, C50.2, C51.1, C51.2, C52.2, C53.2, C54.2, C55.2, C56.2, J1.2, R2.2, R8.2, R13.2, R14.2, R15.2, R18.2, R20.2, R21.2, R22.2, R24.2, R25.2, R26.2, R28.2, R32.2, R34.2, R35.2, R39.2, R41.2, U1.14, U1.25, U1.40, U1.51, U1.60, U1.72, U1.82, U1.93, U1.114, U1.125, U1.136, U1.149, U1.170, U1.184, U1.202, U2.2, U3.6, U3.7, U3.24, U3.29, U3.32, U3.40, U3.45, U3.54, U3.63, U4.10, U4.12, U5.2, U5.8, U6.5, U7.1, U7.9, U7.13, U7.24, U7.25, U8.5, U8.6, U8.7, U8.8, U8.9, U9.1, U11.2, U12.2, U13.4, U13.5, U13.8, U14.1, U14.9, U14.17, U15.2, U16.2, U18.C, U19.1, U19.3, U20.1, U20.3
NET_U1_34: R5.1, U1.34, U20.4
NET_U1_36: R6.1, U1.36, U3.42
NET_U1_42: C23.1, C24.1, F1.1, U1.41, U1.42
NET_U1_45: R7.1, U1.45, U3.41
NET_U1_63: R11.1, U1.63
NET_U1_92: C21.1, U1.92
NET_U1_148: C22.1, U1.148
NET_U1_197: R10.1, U1.197
NET_U1_203: R9.1, U1.203
NET_U1_208: U17.3, U17.4
NET_U2_3: R8.1, U2.3
NET_U3_2: C31.1, C32.1, C33.1, U3.2, U3.55
NET_U3_9: R4.1, U3.9, U19.4
NET_U3_10: R22.1, U3.10
NET_U3_11: R23.1, U3.11
NET_U3_12: R24.1, U3.12
NET_U3_13: R25.1, U3.13
NET_U3_14: R26.1, U3.14
NET_U3_16: R20.1, U3.16
NET_U3_18: R28.1, U3.18
NET_U3_23: R21.1, U3.23
NET_U3_27: C28.1, C29.1, C30.1, U3.22, U3.27, U3.28
NET_U3_37: R27.1, U3.37
NET_U3_38: R18.1, U3.38
NET_U3_39: R19.1, U3.39
NET_U4_1: U3.31, U4.1
NET_U4_2: F2.2, U4.2
NET_U4_3: U3.30, U4.3
NET_U4_4: U3.26, U4.4
NET_U4_5: C27.1, F2.1, U4.2, U4.5
NET_U4_6: U3.25, U4.6
NET_U4_8: R15.1, U4.8
NET_U4_9: R16.1, U4.9
NET_U4_11: R17.1, U4.11
NET_U4_12: R16.2, U4.12
NET_U4_13: R14.1, U4.13, U4.14
NET_U5_6: R29.2, U5.6
NET_U6_2: R29.2, U5.6, U6.2
NET_U6_3: R29.1, U5.7, U6.3
NET_U7_17: R30.1, U7.17
NET_U7_20: R31.1, U7.20
NET_U14_3: C48.2, I1.1, U14.3, U14.4
NET_U14_6: C48.1, U14.6
NET_U14_7: C47.1, U14.7, U14.12
NET_U14_10: R34.1, U14.10
NET_U14_11: R32.1, R33.1, U14.11
NET_U14_ATNET_3: I1.2, R33.2
NET_U15_3: I2.1, U15.3
NET_U15_5: R35.1, R36.1, U15.5
NET_U15_ATNET_3: I2.2, R36.2
NET_U16_1: R38.1, R39.1, U16.1
NET_U16_3: R40.2, R41.1, U16.3
NET_U16_4: R37.1, U16.4, U19.2, U20.2
NET_U17_1: R2.1, U17.1, U17.2
PROC_CAN1_RX: U1.11, U5.4
PROC_CAN1_TX: U1.151, U5.1
PROC_ETH_CRS_DV: U1.56, U3.62
PROC_ETH_RXD0: U1.57, U3.48
PROC_ETH_RXD1: U1.58, U3.47
PROC_ETH_TXD0: U1.104, U3.57
PROC_ETH_TXD1: U1.105, U3.58
PROC_ETH_TX_EN: U1.91, U3.56
PROC_GPIO_TO_U1_USB_FAULT: R12.1, U1.2, U2.6
PROC_GPIO_TO_U1_VBUS_EN: R13.1, U1.1, U2.4
PROC_SPI1_MISO: U1.55, U7.14
PROC_SPI1_MOSI: U1.194, U7.11
PROC_SPI1_NSS: U1.53, U7.12
PROC_SPI1_SCK: U1.54, U7.10
PROC_USB_OTG_FS_DM: U1.145, U8.2, U9.3
PROC_USB_OTG_FS_DP: U1.146, U8.3, U9.2
PROC_USB_OTG_FS_ID: U1.144, U8.4
PROC_USB_OTG_FS_VBUS: U1.143, U2.1, U8.1, U9.4
VCC_S1_5V4: C46.1, C50.1, C53.1, C54.1, J1.1, U14.15, U14.16, U15.4
VCC_TIER1_3V3: C1.1, C2.1, C3.1, C4.1, C5.1, C6.1, C7.1, C8.1, C9.1, C10.1, C11.1, C12.1, C13.1, C14.1, C15.1, C16.1, C17.1, C18.1, C19.1, C20.1, C34.1, C35.1, C36.1, C37.1, C38.1, C40.1, C41.1, C42.1, C43.1, C44.1, C45.1, C49.2, C52.1, C55.1, C56.1, F1.2, I1.2, R4.2, R5.2, R6.2, R7.2, R9.2, R10.2, R11.2, R12.2, R19.2, R23.2, R27.2, R30.2, R31.2, R33.2, R37.2, R38.2, R40.1, U1.6, U1.15, U1.26, U1.39, U1.52, U1.59, U1.73, U1.83, U1.94, U1.103, U1.115, U1.124, U1.137, U1.150, U1.158, U1.171, U1.185, U1.204, U3.1, U3.3, U3.46, U5.5, U7.6, U7.22, U11.4, U12.4, U13.1, U13.2, U14.8, U16.6, U19.5, U20.5
VCC_TIER1_5V0: C39.1, C51.2, I2.2, R36.2, U2.5, U5.3
